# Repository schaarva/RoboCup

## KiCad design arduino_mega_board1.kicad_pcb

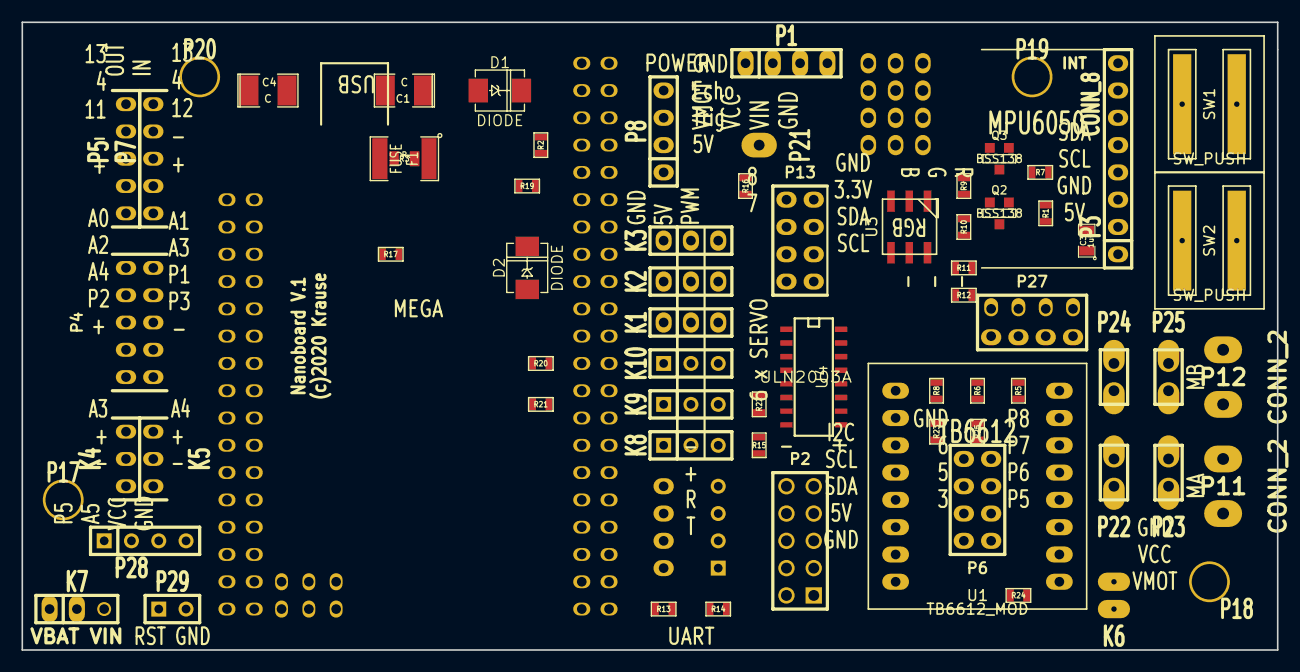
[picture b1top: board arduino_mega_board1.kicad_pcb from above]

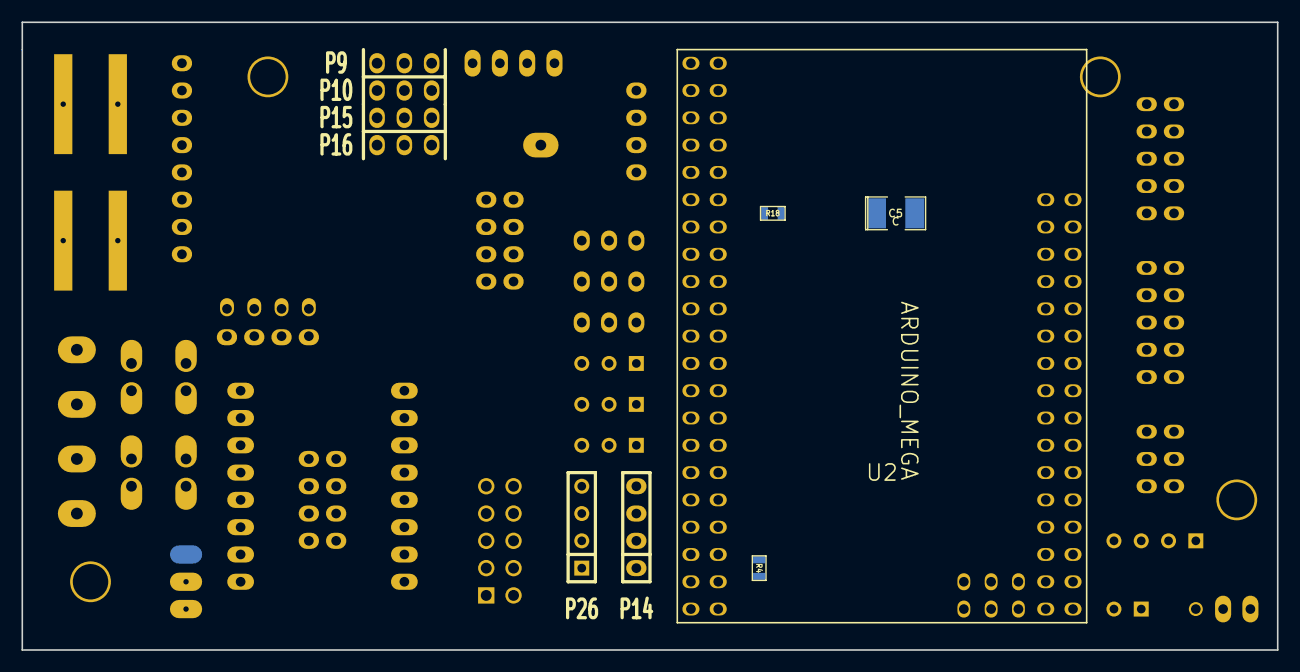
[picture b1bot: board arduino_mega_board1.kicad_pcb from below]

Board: 2 copper layers, 116.8 x 58.4 mm, 79 parts (10 on the bottom side), 79 nets, no tracks yet.

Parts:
C1, C4, C5: C; SM1210L
C3: 1uF; SM0805
D1, D2: DIODE; DO-214AA(SMB)
F1: FUSE; SM1812
K1, K2, K3, K4, K5, K6, K7, K8, K9, K10: CONN_3; SIL-3
P1, P8, P14, P26, P28: CONN_4; SIL-4
P2, P4: CONN_5X2; PIN_ARRAY_5x2
P3: CONN_8; SIL-8
P5, P7: CONN_5; SIL-5
P6, P13, P27: CONN_4X2; pin_array_4x2
P9, P10, P15, P16: CONN_3; SIL-3
P11, P12: CONN_2; bornier2
P17, P18, P19, P20, P21: CONN_1; SIL-1
P22, P23, P24, P25, P29: CONN_2; SIL-2
Q2, Q3: BSS138; SOT23GDS
R1, R7: 10k; SM0603
R2, R4, R5, R6, R8, R9, R10, R11, R12, R13, R14, R15, R17, R18, R19, R20, R21, R22, R23, R24, R25: R; SM0603
R3: R; SM0805
R16: 0; SM0603
SW1, SW2: SW_PUSH; SW_SMD
U1: TB6612_MOD; TB6612_1
U2: ARDUINO_MEGA; Arduino2560Pro
U3: ASMT-YTC2-0AA02; LED_RGB_5050-6
U4: ULN2003A; SO16E

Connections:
/MA1: P11.1, P22.1, P23.1, U1.4
/MA2: P11.2, P22.2, P23.2, U1.5
/MB1: P12.2, P24.1, P25.1, U1.7
/MB2: P12.1, P24.2, P25.2, U1.6
/VUART: P14.3, P26.3, R5.2, R6.2, R14.2, R15.2
BLUE: U2.D32, U3.6
CS_DIS: P5.4, P7.4
GND: C1.2, C3.2, C4.2, C5.2, K4.1, K5.1, P1.4, P2.1, P2.2, P3.2, P4.1, P5.2, P6.8, P7.2, P8.4, P13.1, P13.2, P14.4, P21.1, P26.4, P28.4, P29.2, R2.2, R8.2, R9.1, R10.1, R11.1, R12.1, R16.1, R17.2, R21.2, R23.2, R25.2, U2.GND, U4.8
GREEN: U2.D31, U3.5
I2C_SEL1: P2.9, R20.2, R21.1
I2C_SEL2: P2.10, R22.2, R23.1
LED1: P4.5, U2.D23, U4.7
LED2: P4.4, U2.D24, U4.6
LED3: P4.3, U2.D25, U4.5
LED4: U2.D26, U4.4
LED5: U2.D27, U4.3
LED6: U2.D28, U4.2
LED7: U2.D29, U4.1
LS1: P4.10, U2.A0
LS2: P4.9, U2.A1
LS3: P4.8, U2.A2
LS4: K5.3, P4.7, U2.A3
LS5: K4.3, P4.6, U2.A4
LS6: P28.2, U2.A5
MGND: K1.1, K2.1, K3.1, K6.3, K8.1, K9.1, K10.1, R16.2, U1.3
MPU_INT: P3.8, U2.D38
unnamed: P26.1, R4.2
unnamed: P14.1, R13.2
unnamed: D1.2, D2.1
unnamed: R2.1, U3.3
unnamed: R17.1, U3.1
unnamed: R18.2, R19.1, U1.13
unnamed: R8.1, U3.2
unnamed: P1.2, P1.3
O1: P6.1, U1.15, U2.D33
O2: P6.3, U1.14, U2.D34
O3: P6.5, U1.12, U2.D36
O4: P6.7, U1.11, U2.D37
P1: P10.1, P10.2, U4.10
P2: P15.1, P15.2, U4.11
P3: P16.1, P16.2, U4.12
P4: P10.3, U4.13
P5: P15.3, P28.1, U4.14
P6: P16.3, U4.15
PWMA: P6.2, U1.16, U2.D9
PWMB: P6.4, U1.10, U2.D10
PWMSERVO1: K8.3, U2.D2
PWMSERVO2: K9.3, U2.D3
PWMSERVO3: K10.3, U2.D5
PWMSERVO4: K1.3, U2.D6
PWMSERVO5: K2.3, U2.D7
PWMSERVO6: K3.3, U2.D8
RED: U2.D30, U3.4
RST: P29.1, U2.RST
RX2: P14.2, U2.D17
RX3: P26.2, U2.D15
SCK: P5.5, P7.5
SCL: P2.7, P2.8, P3.3, Q2.D, R1.2, U2.D21
SCL33: P13.7, P13.8, Q2.S
SDA: P2.5, P2.6, P3.4, Q3.D, R7.2, U2.D20
SDA33: P13.5, P13.6, Q3.S
SEL5_1: R20.1, U2.D12
SEL5_2: R22.1, U2.D11
STBY: R19.2, U2.D35
SW1: P27.2, R9.2, SW1.2, U2.D50
SW2: P27.4, R10.2, SW2.2, U2.D51
SW3: P27.6, R11.2, U2.D52
SW4: P27.8, R12.2, U2.D53
TX2: R13.1, U2.D16
TX3: R4.1, U2.D14
US_Echo: P8.3, U2.D47
US_TRIG: P8.2, U2.D46
V33: C5.1, P13.3, P13.4, Q2.G, Q3.G, R6.1, R15.1, U2.V33
VBAT: K7.1, P1.1
VCC: C3.1, C4.1, K4.2, K5.2, K6.2, P2.3, P2.4, P3.1, P4.2, P5.1, P7.1, P8.1, P9.1, P9.2, P9.3, P27.1, P27.3, P27.5, P27.7, P28.3, R1.1, R5.1, R7.1, R14.1, R18.1, SW1.1, SW2.1, U1.2, U2.V5, U4.9
VIN: C1.1, D1.1, F1.1, K6.1, K7.2, R3.1, R24.1, U1.1, U2.VIN
VIN1: F1.2, R3.2
VIN_MESS: R24.2, R25.1, U2.A6
VSERVO: D2.2, K1.2, K2.2, K3.2, K8.2, K9.2, K10.2

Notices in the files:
arduino_mega_board1.kicad_pcb:
(c)2020 Krause
